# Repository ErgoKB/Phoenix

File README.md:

# Phoenix

Phoenix is inspired by [Ergodox](https://www.ergodox.io/), and add several improvements on it.

## Features

* A split ergonomic keyboard which fits the shape of the hands of human
* Improve the keyboard performance and response time of Ergodox by using dual controller
* Dual connectivity of both left and right hands can connect to USB host without re-program the mcu
* Use USB C connectors
* Use hotswap switch connectors to get rid of soldering
* A single PCB design for both left and right hand
* A more stable PCB mounting design
* Use parts that are can be obtained more easily

## How to build

Still in progress

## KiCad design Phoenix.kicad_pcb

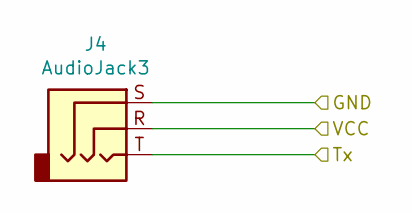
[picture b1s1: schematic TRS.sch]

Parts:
J4: AudioJack3; PJ322_TRS

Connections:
/TRS/Tx: J4.T; also elsewhere on the board
/TRS/VCC: J4.R; also elsewhere on the board
GNDPWR: J4.S; also elsewhere on the board

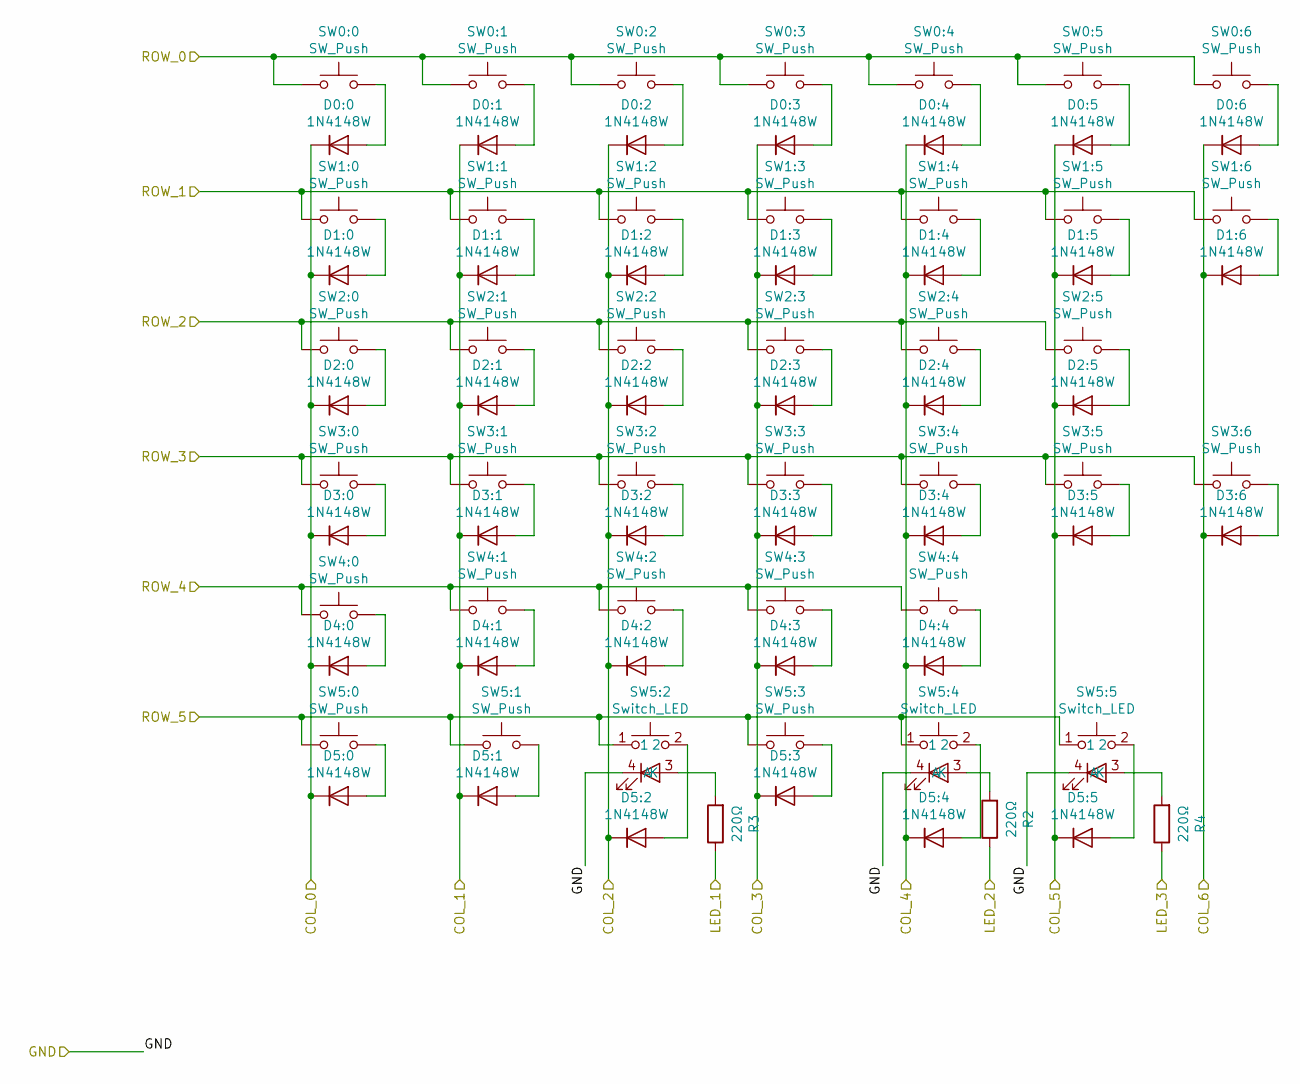
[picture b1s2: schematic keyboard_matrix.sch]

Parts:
D0:0, D0:1, D0:2, D0:3, D0:4, D0:5, D0:6, D1:0, D1:1, D1:2, D1:3, D1:4, D1:5, D1:6, D2:0, D2:1, D2:2, D2:3, D2:4, D2:5, D3:0, D3:1, D3:2, D3:3, D3:4, D3:5, D3:6, D4:0, D4:1, D4:2, D4:3, D4:4, D5:0, D5:1, D5:2, D5:3, D5:4, D5:5: 1N4148W; D_SOD-123
R2, R3, R4: 220Ω; R_0603_1608Metric
SW0:0, SW0:1, SW0:2, SW0:3, SW0:4, SW0:5, SW0:6, SW1:0, SW1:1, SW1:2, SW1:3, SW1:4, SW1:5, SW1:6, SW2:0, SW2:1, SW2:2, SW2:3, SW2:4, SW2:5, SW3:0, SW3:1, SW3:2, SW3:3, SW3:4, SW3:5, SW3:6, SW4:0, SW4:1, SW4:2, SW4:3, SW4:4, SW5:0, SW5:1, SW5:3: SW_Push; Kailh_hot_socket_MX_dual
SW5:2, SW5:4, SW5:5: Switch_LED; Kailh_hot_socket_MX_dual_led

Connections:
/keyboard_matrix/COL_0: D0:0.1 (K), D1:0.1 (K), D2:0.1 (K), D3:0.1 (K), D4:0.1 (K), D5:0.1 (K); also elsewhere on the board
/keyboard_matrix/COL_1: D0:1.1 (K), D1:1.1 (K), D2:1.1 (K), D3:1.1 (K), D4:1.1 (K), D5:1.1 (K); also elsewhere on the board
/keyboard_matrix/COL_2: D0:2.1 (K), D1:2.1 (K), D2:2.1 (K), D3:2.1 (K), D4:2.1 (K), D5:2.1 (K); also elsewhere on the board
/keyboard_matrix/COL_3: D0:3.1 (K), D1:3.1 (K), D2:3.1 (K), D3:3.1 (K), D4:3.1 (K), D5:3.1 (K); also elsewhere on the board
/keyboard_matrix/COL_4: D0:4.1 (K), D1:4.1 (K), D2:4.1 (K), D3:4.1 (K), D4:4.1 (K), D5:4.1 (K); also elsewhere on the board
/keyboard_matrix/COL_5: D0:5.1 (K), D1:5.1 (K), D2:5.1 (K), D3:5.1 (K), D5:5.1 (K); also elsewhere on the board
/keyboard_matrix/COL_6: D0:6.1 (K), D1:6.1 (K), D3:6.1 (K); also elsewhere on the board
/keyboard_matrix/LED_1: R3.1; also elsewhere on the board
/keyboard_matrix/LED_2: R2.1; also elsewhere on the board
/keyboard_matrix/LED_3: R4.1; also elsewhere on the board
/keyboard_matrix/ROW_0: SW0:0.1, SW0:1.1, SW0:2.1, SW0:3.1, SW0:4.1, SW0:5.1, SW0:6.1; also elsewhere on the board
/keyboard_matrix/ROW_1: SW1:0.1, SW1:1.1, SW1:2.1, SW1:3.1, SW1:4.1, SW1:5.1, SW1:6.1; also elsewhere on the board
/keyboard_matrix/ROW_2: SW2:0.1, SW2:1.1, SW2:2.1, SW2:3.1, SW2:4.1, SW2:5.1; also elsewhere on the board
/keyboard_matrix/ROW_3: SW3:0.1, SW3:1.1, SW3:2.1, SW3:3.1, SW3:4.1, SW3:5.1, SW3:6.1; also elsewhere on the board
/keyboard_matrix/ROW_4: SW4:0.1, SW4:1.1, SW4:2.1, SW4:3.1, SW4:4.1; also elsewhere on the board
/keyboard_matrix/ROW_5: SW5:0.1, SW5:1.1, SW5:2.1, SW5:3.1, SW5:4.1, SW5:5.1; also elsewhere on the board
GNDPWR: SW5:2.4 (K), SW5:4.4 (K), SW5:5.4 (K); also elsewhere on the board
unnamed: D0:0.2 (A), SW0:0.2
unnamed: D0:1.2 (A), SW0:1.2
unnamed: D0:2.2 (A), SW0:2.2
unnamed: D0:3.2 (A), SW0:3.2
unnamed: D0:4.2 (A), SW0:4.2
unnamed: D0:5.2 (A), SW0:5.2
unnamed: D0:6.2 (A), SW0:6.2
unnamed: D1:0.2 (A), SW1:0.2
unnamed: D1:1.2 (A), SW1:1.2
unnamed: D1:2.2 (A), SW1:2.2
unnamed: D1:3.2 (A), SW1:3.2
unnamed: D1:4.2 (A), SW1:4.2
unnamed: D1:5.2 (A), SW1:5.2
unnamed: D1:6.2 (A), SW1:6.2
unnamed: D2:0.2 (A), SW2:0.2
unnamed: D2:1.2 (A), SW2:1.2
unnamed: D2:2.2 (A), SW2:2.2
unnamed: D2:3.2 (A), SW2:3.2
unnamed: D2:4.2 (A), SW2:4.2
unnamed: D2:5.2 (A), SW2:5.2
unnamed: D3:0.2 (A), SW3:0.2
unnamed: D3:1.2 (A), SW3:1.2
unnamed: D3:2.2 (A), SW3:2.2
unnamed: D3:3.2 (A), SW3:3.2
unnamed: D3:4.2 (A), SW3:4.2
unnamed: D3:5.2 (A), SW3:5.2
unnamed: D3:6.2 (A), SW3:6.2
unnamed: D4:0.2 (A), SW4:0.2
unnamed: D4:1.2 (A), SW4:1.2
unnamed: D4:2.2 (A), SW4:2.2
unnamed: D4:3.2 (A), SW4:3.2
unnamed: D4:4.2 (A), SW4:4.2
unnamed: D5:0.2 (A), SW5:0.2
unnamed: D5:1.2 (A), SW5:1.2
unnamed: D5:2.2 (A), SW5:2.2
unnamed: D5:3.2 (A), SW5:3.2
unnamed: D5:4.2 (A), SW5:4.2
unnamed: D5:5.2 (A), SW5:5.2
unnamed: R2.2, SW5:4.3 (A)
unnamed: R3.2, SW5:2.3 (A)
unnamed: R4.2, SW5:5.3 (A)

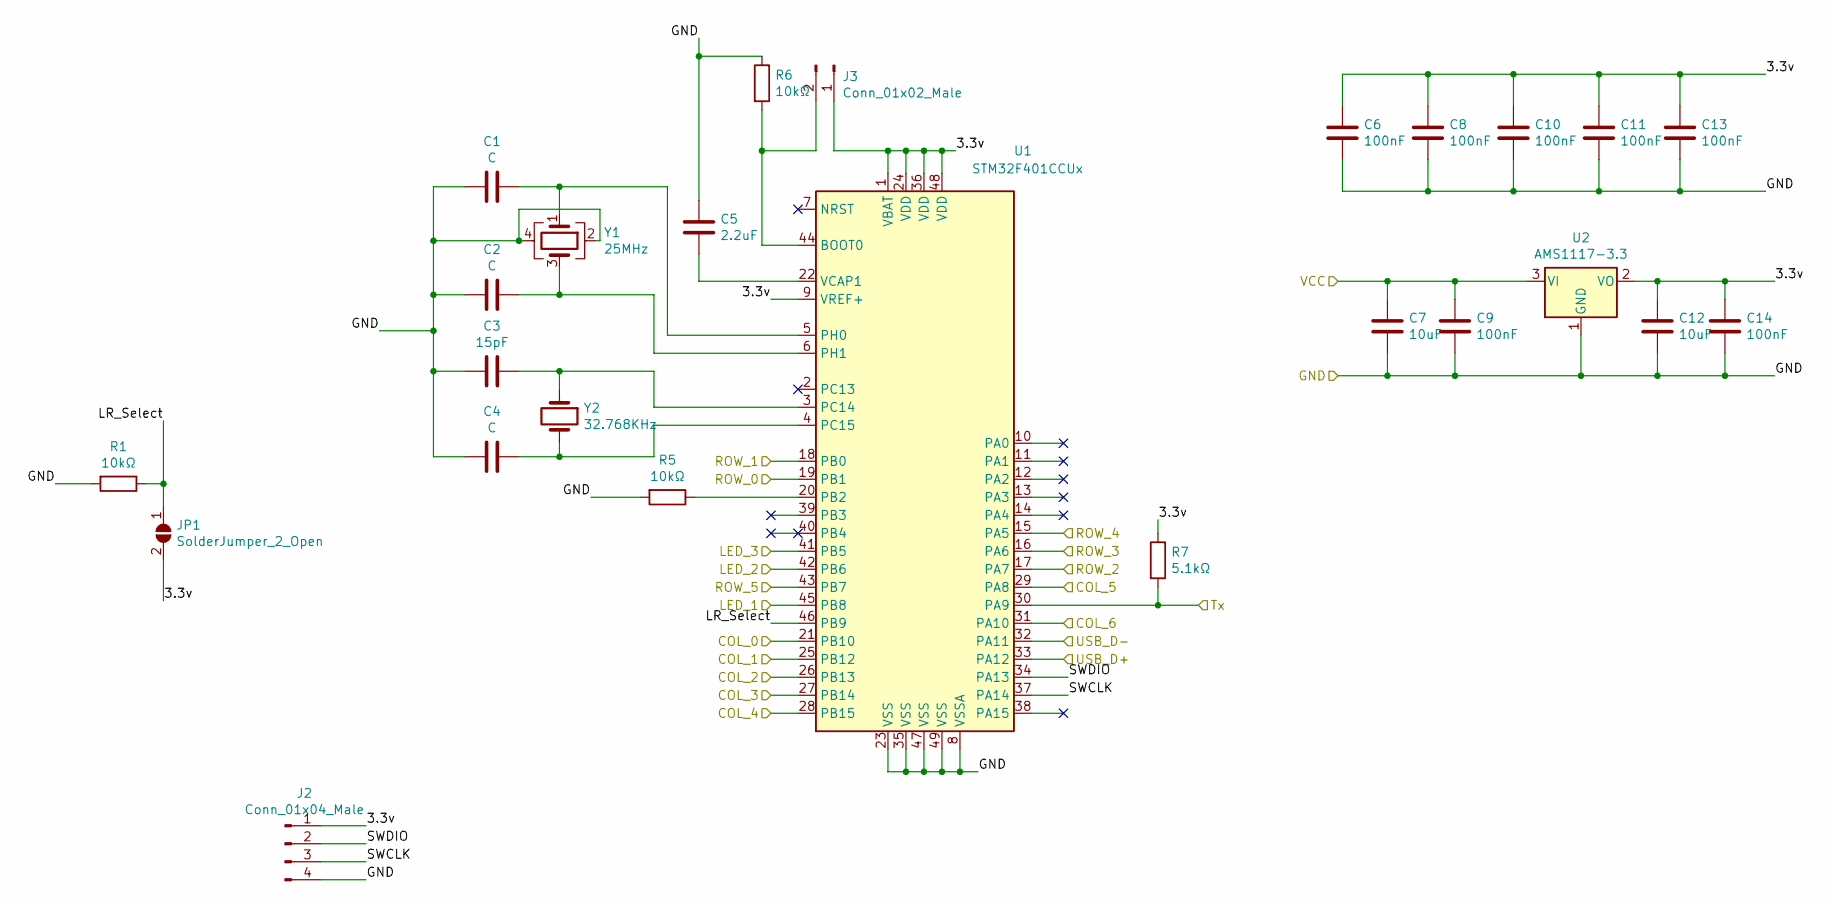
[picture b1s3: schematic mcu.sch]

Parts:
C1, C2, C4: C; C_0402_1005Metric
C3: 15pF; C_0402_1005Metric
C5: 2.2uF; C_0805_2012Metric
C6, C8, C9, C10, C11, C13, C14: 100nF; C_0402_1005Metric
C7, C12: 10uF; C_0805_2012Metric
J2: Conn_01x04_Male; PinSocket_1x04_P2.54mm_Vertical
J3: Conn_01x02_Male; PinSocket_1x02_P2.54mm_Vertical
JP1: SolderJumper_2_Open; SolderJumper-2_P1.3mm_Open_Pad1.0x1.5mm
R1, R5, R6: 10kΩ; R_1206_3216Metric
R7: 5.1kΩ; R_0603_1608Metric
U1: STM32F401CCUx; QFN-48-1EP_7x7mm_P0.5mm_EP5.6x5.6mm
U2: AMS1117-3.3; SOT-223-3_TabPin2
Y1: 25MHz; Crystal_SMD_3225-4Pin_3.2x2.5mm
Y2: 32.768KHz; Crystal_SMD_3215-2Pin_3.2x1.5mm

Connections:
/TRS/Tx: R7.2, U1.30 (PA9); also elsewhere on the board
/TRS/VCC: C7.1, C9.1, U2.3 (VI); also elsewhere on the board
/keyboard_matrix/COL_0: U1.21 (PB10); also elsewhere on the board
/keyboard_matrix/COL_1: U1.25 (PB12); also elsewhere on the board
/keyboard_matrix/COL_2: U1.26 (PB13); also elsewhere on the board
/keyboard_matrix/COL_3: U1.27 (PB14); also elsewhere on the board
/keyboard_matrix/COL_4: U1.28 (PB15); also elsewhere on the board
/keyboard_matrix/COL_5: U1.29 (PA8); also elsewhere on the board
/keyboard_matrix/COL_6: U1.31 (PA10); also elsewhere on the board
/keyboard_matrix/LED_1: U1.45 (PB8); also elsewhere on the board
/keyboard_matrix/LED_2: U1.42 (PB6); also elsewhere on the board
/keyboard_matrix/LED_3: U1.41 (PB5); also elsewhere on the board
/keyboard_matrix/ROW_0: U1.19 (PB1); also elsewhere on the board
/keyboard_matrix/ROW_1: U1.18 (PB0); also elsewhere on the board
/keyboard_matrix/ROW_2: U1.17 (PA7); also elsewhere on the board
/keyboard_matrix/ROW_3: U1.16 (PA6); also elsewhere on the board
/keyboard_matrix/ROW_4: U1.15 (PA5); also elsewhere on the board
/keyboard_matrix/ROW_5: U1.43 (PB7); also elsewhere on the board
/mcu/3.3v: C6.1, C8.1, C10.1, C11.1, C12.1, C13.1, C14.1, J2.1, J3.1, JP1.2 (B), R7.1, U1.1 (VBAT), U1.9 (VREF+), U1.24 (VDD), U1.36 (VDD), U1.48 (VDD), U2.2 (VO)
/mcu/LR_Select: JP1.1 (A), R1.1, U1.46 (PB9)
/mcu/SWCLK: J2.3, U1.37 (PA14)
/mcu/SWDIO: J2.2, U1.34 (PA13)
/usb_c/D+: U1.33 (PA12); also elsewhere on the board
/usb_c/D-: U1.32 (PA11); also elsewhere on the board
GNDPWR: C1.2, C2.2, C3.2, C4.2, C5.2, C6.2, C7.2, C8.2, C9.2, C10.2, C11.2, C12.2, C13.2, C14.2, J2.4, R1.2, R5.2, R6.1, U1.8 (VSSA), U1.23 (VSS), U1.35 (VSS), U1.47 (VSS), U1.49 (VSS), U2.1 (GND), Y1.2, Y1.4; also elsewhere on the board
unnamed: C1.1, U1.5 (PH0), Y1.1
unnamed: C2.1, U1.6 (PH1), Y1.3
unnamed: C3.1, U1.3 (PC14), Y2.1
unnamed: C4.1, U1.4 (PC15), Y2.2
unnamed: C5.1, U1.22 (VCAP1)
unnamed: J3.2, R6.2, U1.44 (BOOT0)
unnamed: R5.1, U1.20 (PB2)

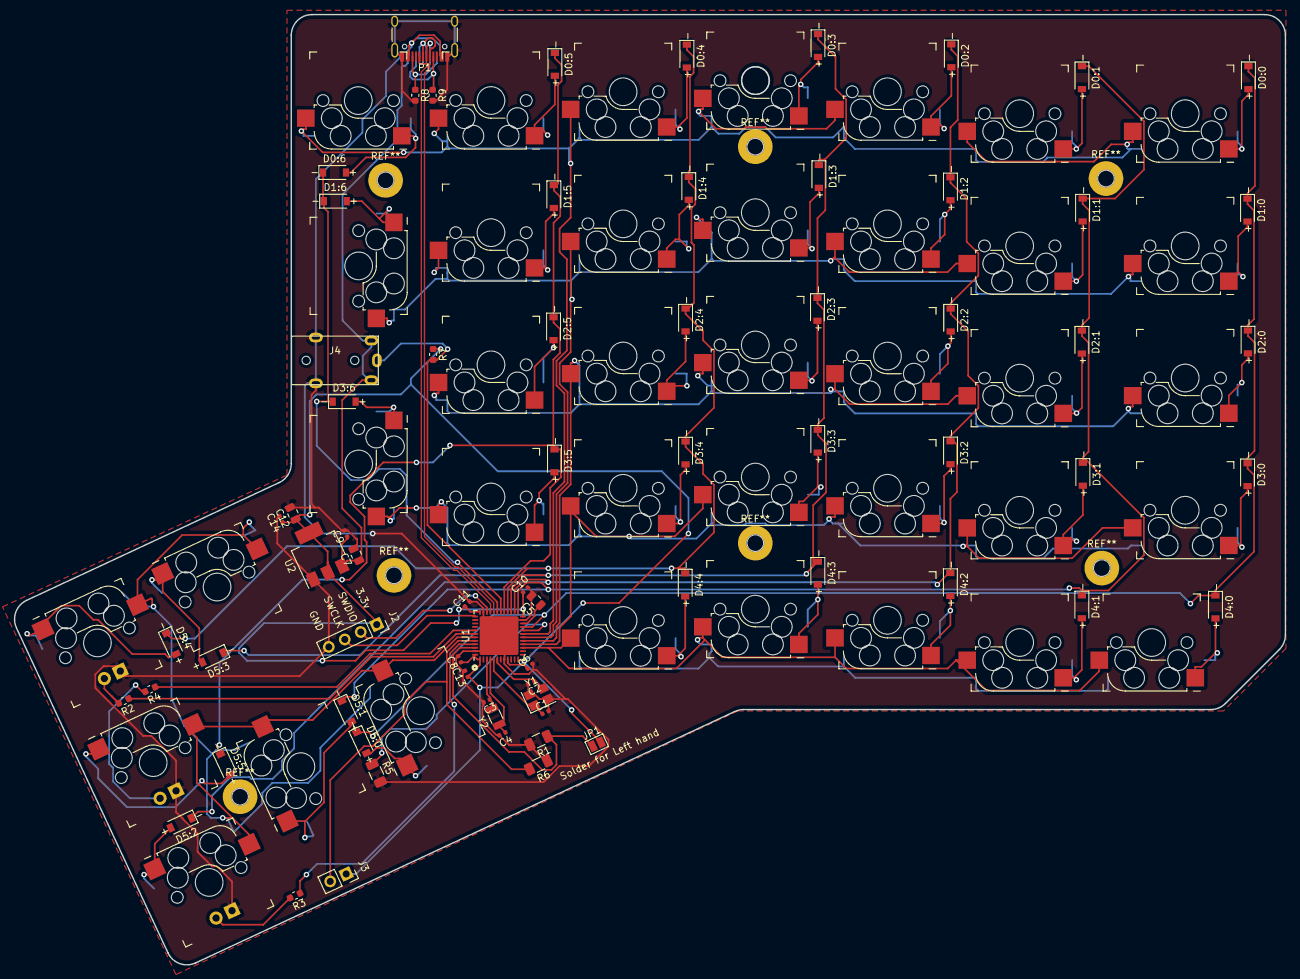
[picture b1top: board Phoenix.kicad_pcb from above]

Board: 2 copper layers, 183.2 x 137.0 mm, 108 parts (0 on the bottom side), 75 nets.

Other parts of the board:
P1: USB_C_Receptacle_USB2.0; USB_C_Receptacle_HRO_TYPE-C-31-M-12-Dual
R8, R9: 5.1kΩ; R_0603_1608Metric

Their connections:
/TRS/VCC: P1.A4, P1.A9, P1.B4, P1.B9; also elsewhere on the board
/usb_c/D+: P1.A6, P1.B6; also elsewhere on the board
/usb_c/D-: P1.A7, P1.B7; also elsewhere on the board
GNDPWR: P1.A1, P1.A12, P1.B1, P1.B12, P1.S1, R8.2, R9.2; also elsewhere on the board
unnamed: P1.A5, R9.1
unnamed: P1.B5, R8.1

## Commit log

2020-07-10 Create LICENSE
